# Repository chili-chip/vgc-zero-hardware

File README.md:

# chilichip console hardware (VGC Zero)

KiCad 10 project for the main board of [chilichip](https://chilichip.eu)'s open hardware keychain game console, the **VGC Zero**. A Waveshare RP2350-Plus runs the console and charges its LiPo; the display, buttons, audio and Wi-Fi/Bluetooth are modules that solder or plug onto this board. Firmware and games are built with the [chili-chip 32blit SDK](https://github.com/chili-chip/32blit-sdk) (board `chilichip_vgc`).

**Documentation: [hardware.chilichip.eu](https://hardware.chilichip.eu)** (specifications, pin map, modules, build guide). Source in [`docs/`](docs/).

Current revision: **v3.0.0**. The schematic (`vgc-zero.kicad_sch`) is the source of truth for everything below.

| Front | Back |
|:---:|:---:|
|  |  |

## Specifications

| | |
|---|---|
| Board | 50 × 100 mm, 2 layers, 1.6 mm, GND pour on both layers. About 19 mm thick assembled (display front to battery back) |
| MCU | [Waveshare RP2350-Plus](https://www.waveshare.com/wiki/RP2350-Plus) (RP2350A, USB-C, Pico-compatible pinout), soldered flat on the back by its castellated edge |
| Display | Waveshare 1.5" RGB OLED (SSD1351, 128 × 128, SPI) on the front |
| Buttons | [chili-buttons-module](https://github.com/chili-chip/chili-buttons-module-hardware): D-pad, A/B, X/Y, Start/Select, soldered flat on the front |
| Audio | [chili-audio-module](https://github.com/chili-chip/chili-audio-module-hardware): MAX98357A I²S class D amplifier, soldered flat on the back |
| Sensors | [chili-utility-module](https://github.com/chili-chip/chili-utility-module-hardware): 6-axis IMU, RTC backed by the LiPo (through VSYS), SMD haptic motor, all on I²C; soldered flat on the back beside the MCU |
| Wireless | Raspberry Pi Radio Module 2 (RM2, CYW43439): Wi-Fi 4 and Bluetooth 5.2, on the back with its antenna at the bottom edge over a copper keep-out |
| Power | 1-cell LiPo, LP802540 (8.0 × 25 × 40 mm, ~800 mAh), flat on the back between the MCU and the RM2. It plugs into the RP2350-Plus's PH1.25 battery header and charges from USB-C at 1 A, about 1.25C; replace R13 on the RP2350-Plus (160 kΩ) with about 200 kΩ to charge at about 0.8 A (1C). The RP2350-Plus's 3.3 V output supplies all modules |

## Parts

| Ref | Part | Side | Notes |
|-----|------|------|-------|
| U1 | [Waveshare RP2350-Plus](https://www.waveshare.com/wiki/RP2350-Plus) | back | `vgc-zero-footprints:RP2350-Plus`: the Pico hand-solder lands without the SWD pads, plus clearance holes for the USB-C shell legs and pegs under the module |
| U2 | [chili-audio-module](https://github.com/chili-chip/chili-audio-module-hardware) v1.1+ | back | castellated, 11.5 × 17.5 mm |
| U3 | [Raspberry Pi Radio Module 2](https://www.raspberrypi.com/products/radio-module-2/) | back | `RF_Module:RMC20452T` |
| U4 | [Waveshare 1.5inch RGB OLED Module](https://www.waveshare.com/wiki/1.5inch_RGB_OLED_Module) | front | 7-pin 2.54 mm header plus four mounting holes |
| U5 | [chili-buttons-module](https://github.com/chili-chip/chili-buttons-module-hardware) v1.2+ | front | castellated, 50 × 39 mm |
| U6 | [chili-utility-module](https://github.com/chili-chip/chili-utility-module-hardware) v2.0+ | back | castellated, 16.4 × 14.8 mm, six lands; between the MCU, R2/R3, a display mounting hole and the battery |
| BT1 | LiPo LP802540, ~800 mAh, with PCM and a PH1.25 2-pin plug | back | stuck down with double-sided tape; plugs into U1's battery header. Board-only footprint for its outline and 3D model |
| R2 | 470 Ω, axial | back | RM2 DO to the shared data line |
| R3 | 10 kΩ, axial | back | RM2 nIRQ to the shared data line |

The RM2 is wired like the Pico W radio: one GPIO (WIFI_DIO) drives DI directly and reads DO and nIRQ through R2 and R3.

## Pin map

GPIOs were chosen so every trace runs as short and straight as possible to its module. The display sits on hardware SPI1, and the Wi-Fi signals sit on SPI1's SCK/TX/CSn pins; the RM2's driver (cyw43) runs it from PIO.

| GPIO | Module pin | Signal | Notes |
|------|----------|--------|-------|
| GP0 | 1 | UTIL_SDA | I2C0 SDA; pull-up on the module |
| GP1 | 2 | UTIL_SCL | I2C0 SCL; pull-up on the module |
| GP2 | 4 | UTIL_INT | open-drain IMU/RTC interrupt; pull-up on the module |
| GP3 | 5 | AUDIO_DIN | I²S data |
| GP4 | 6 | AUDIO_BCLK | I²S bit clock |
| GP5 | 7 | AUDIO_LRCLK | I²S word select (BCLK + 1, as the PIO I²S driver expects) |
| GP6 | 9 | AUDIO_MODE | amplifier enable (high = on, mono mix) |
| GP7 | 10 | BTN_A | |
| GP8 | 11 | BTN_B | |
| GP9 | 12 | WIFI_ON | RM2 WL_ON and BT_ON |
| GP10 | 14 | BTN_Y | |
| GP11 | 15 | BTN_X | |
| GP12 | 16 | BTN_SELECT | |
| GP13 | 17 | WIFI_CS | SPI1 CSn |
| GP14 | 19 | WIFI_CLK | SPI1 SCK |
| GP15 | 20 | WIFI_DIO | SPI1 TX; DI direct, DO via R2, nIRQ via R3 |
| GP16 | 21 | BTN_DOWN | |
| GP17 | 22 | BTN_RIGHT | |
| GP18 | 24 | BTN_START | |
| GP19 | 25 | BTN_UP | |
| GP20 | 26 | BTN_LEFT | |
| GP21 | 27 | DISP_RST | |
| GP22 | 29 | DISP_DC | |
| GP26 | 31 | DISP_CLK | SPI1 SCK |
| GP27 | 32 | DISP_DIN | SPI1 TX |
| GP28 | 34 | DISP_CS | |

The utility module's RTC backup (VBAT, land 6) is wired to VSYS (RP2350-Plus pin 39), which stays powered from the LiPo while the console is off. The utility module takes GP0/GP1, the default UART0 pins, so use USB serial for debug output. Its I²C addresses are 0x6A (IMU), 0x52 (RTC) and 0x5A (haptic driver). Buttons short to GND when pressed and have no pull-ups on the module, so enable the RP2350's internal pull-ups.

## Ordering the PCB from JLCPCB

Every tagged release has `chilichip-console-<version>-gerbers.zip` (Gerbers and drill) and `chilichip-console-<version>-bom.csv` (hand-assembly BOM) attached.

1. Download the gerber zip from the [latest release](https://github.com/chili-chip/vgc-zero-hardware/releases/latest).
2. On [jlcpcb.com](https://jlcpcb.com/), click **Order now** and upload the zip.
3. Choose 2 layers and 1.6 mm thickness. HASL is fine; ENIG is nicer for soldering the castellated modules flat. Everything else can stay at the defaults.
4. Leave **PCB Assembly** off: every part on this board is soldered by hand.

The audio, buttons and utility modules are separate boards. Order them from their own repositories.

To build the files from a local checkout instead, run `scripts/export-jlcpcb.sh` (needs KiCad 10's `kicad-cli` and `zip`). They're written to `production/`.

## Assembly

1. **Back side:** solder the RP2350-Plus flat by its castellations, then the RM2, the audio module, the utility module and R2/R3. Stick the LiPo down in its outline and plug it into the RP2350-Plus's battery header.
2. **Front side:** solder the buttons module flat by its castellations, then fit the display on its 7-pin header and fix it with the four mounting holes.
3. Keep the area past the RM2's antenna clear: no metal, cables or fingers over the keep-out at the bottom edge.

## Repository layout

| Path | Contents |
|------|----------|
| `vgc-zero.kicad_*` | KiCad 10 schematic, PCB and project |
| `vgc-zero-symbols.kicad_sym`, `vgc-zero-footprints.pretty/` | Project symbols and footprints (module outlines and castellation lands) |
| `RPI_RMC20452T.kicad_sym` | Official RM2 symbol from Raspberry Pi |
| `3d-models/` | STEP models of the modules (display, audio, buttons, utility, RM2), the RP2350-Plus (Waveshare's model, gzipped as `.stpZ`) and the LiPo envelope |
| `vgc-zero.glb` | 3D export of the assembled board |
| `scripts/export-jlcpcb.sh` | Builds the gerber zip and BOM |
| `scripts/render-images.sh` | Regenerates the renders, placement drawings and schematic in `docs/`, and `vgc-zero.glb` |
| `docs/`, `mkdocs.yml` | Documentation site ([hardware.chilichip.eu](https://hardware.chilichip.eu)) |
| `docs/next-revision.md` | The plan this revision implemented |
| `.github/workflows/main.yml` | CI and release workflow |
| `.github/workflows/docs.yml` | Builds the docs site and deploys it to Cloudflare Pages |

CI runs ERC, DRC and the JLCPCB export on every push and pull request. Pushing a `v*` tag publishes a GitHub release with the schematic PDF, a PCB image, Gerbers and the JLCPCB files.

## Earlier revisions

Board v2.0.0 (50 × 90 mm) used a Raspberry Pi Pico 2 and USB power only, with no battery and no utility module.

Board v1.1.4 used a Waveshare RP2350-Plus, ten through-hole tactile buttons, a buzzer, an LED and a JST cable to the display. The first prototype was built on a breadboard: see the [breadboard guide](https://chilichip.eu/docs/vgc-zero/vgc-breadboard/).

## License

MIT, see [LICENSE](LICENSE).

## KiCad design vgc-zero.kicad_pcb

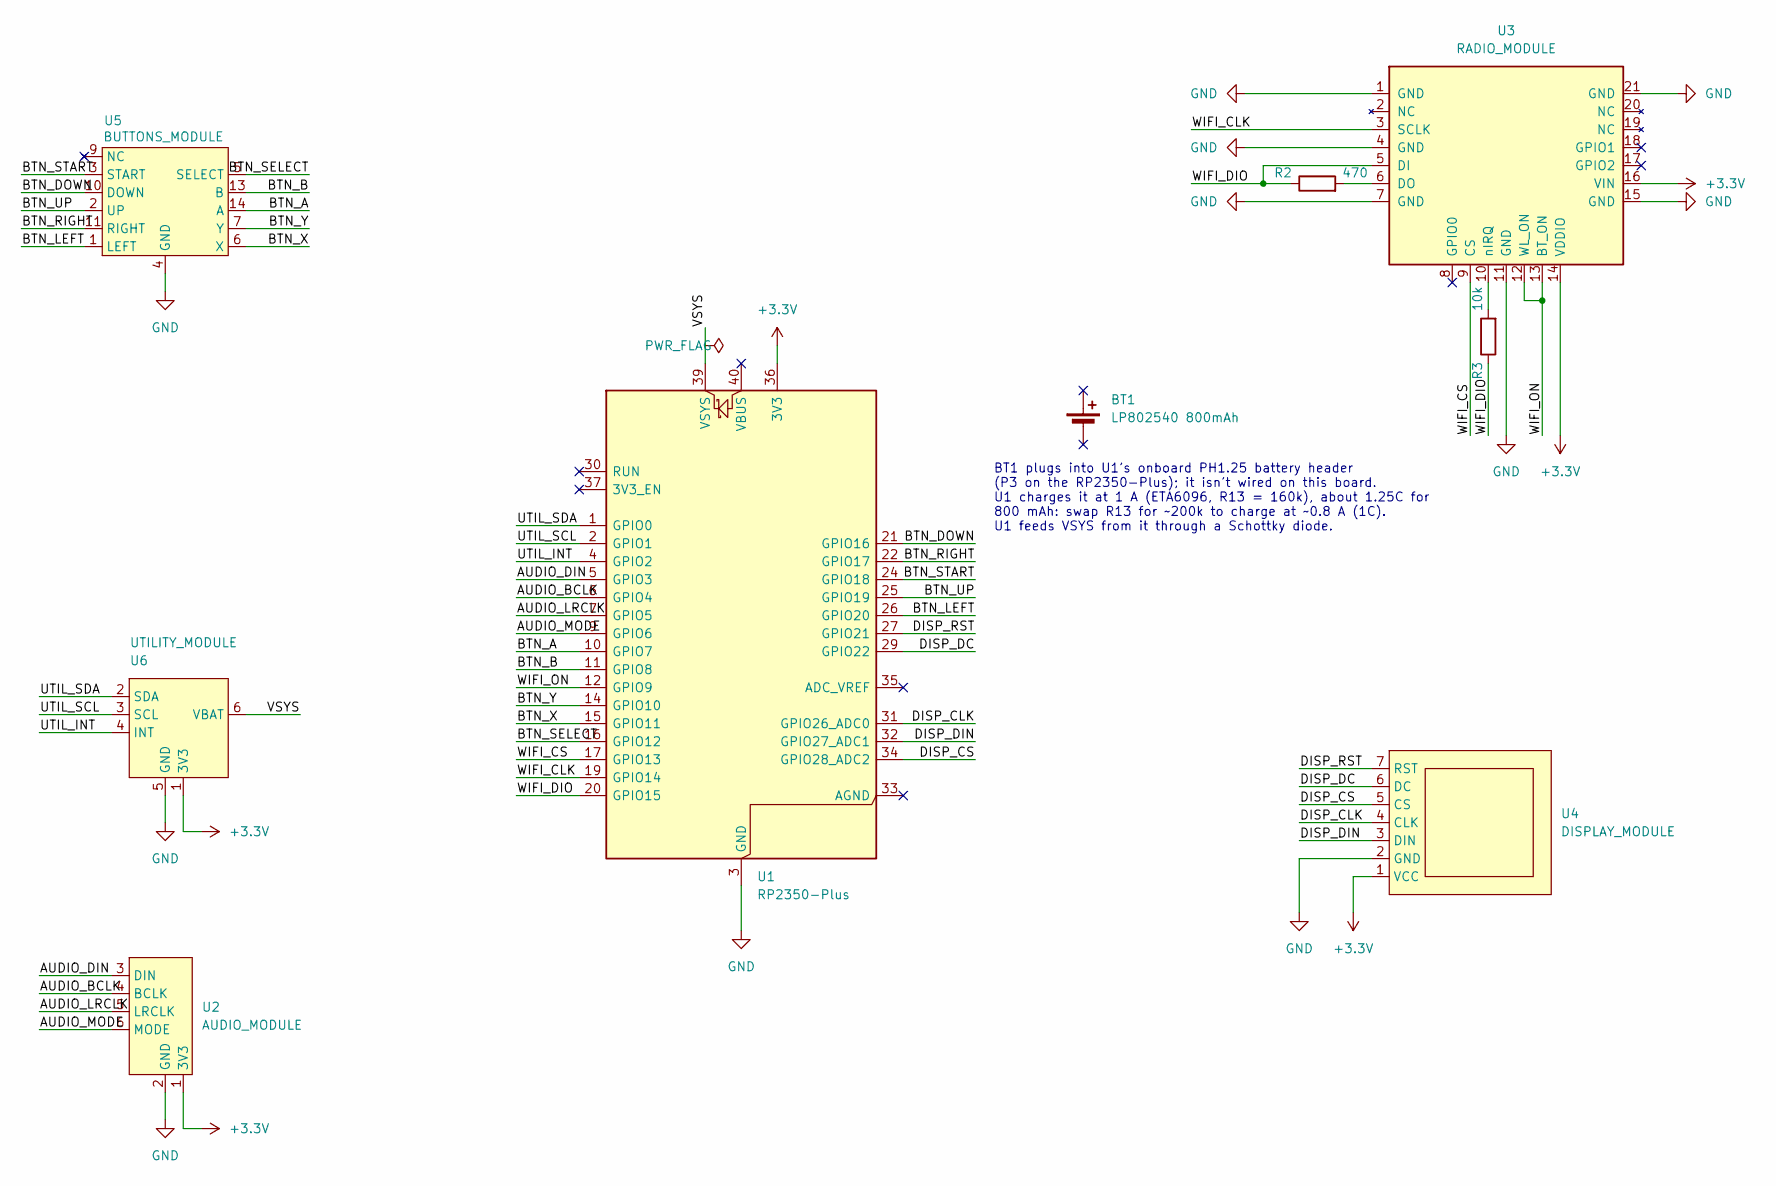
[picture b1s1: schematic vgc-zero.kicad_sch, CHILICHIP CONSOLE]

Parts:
BT1: LP802540 800mAh; LiPo_LP802540
R2: 470; R_Axial_DIN0207_L6.3mm_D2.5mm_P10.16mm_Horizontal
R3: 10k; R_Axial_DIN0207_L6.3mm_D2.5mm_P10.16mm_Horizontal
U1: RP2350-Plus
U2: AUDIO_MODULE; AudioModule
U3: RADIO_MODULE; RMC20452T
U4: DISPLAY_MODULE; SSD1351_OLED_128x128_WAVESHARE
U5: BUTTONS_MODULE; ButtonsModule
U6: UTILITY_MODULE; UtilityModule

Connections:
+3.3V: U1.36 (3V3), U2.1 (3V3), U3.14 (VDDIO), U3.16 (VIN), U4.1 (VCC), U6.1 (3V3)
/AUDIO_BCLK: U1.6 (GPIO4), U2.4 (BCLK)
/AUDIO_DIN: U1.5 (GPIO3), U2.3 (DIN)
/AUDIO_LRCLK: U1.7 (GPIO5), U2.5 (LRCLK)
/AUDIO_MODE: U1.9 (GPIO6), U2.6 (MODE)
/BTN_A: U1.10 (GPIO7), U5.14 (A)
/BTN_B: U1.11 (GPIO8), U5.13 (B)
/BTN_DOWN: U1.21 (GPIO16), U5.10 (DOWN)
/BTN_LEFT: U1.26 (GPIO20), U5.1 (LEFT)
/BTN_RIGHT: U1.22 (GPIO17), U5.11 (RIGHT)
/BTN_SELECT: U1.16 (GPIO12), U5.5 (SELECT)
/BTN_START: U1.24 (GPIO18), U5.3 (START)
/BTN_UP: U1.25 (GPIO19), U5.2 (UP)
/BTN_X: U1.15 (GPIO11), U5.6 (X)
/BTN_Y: U1.14 (GPIO10), U5.7 (Y)
/DISP_CLK: U1.31 (GPIO26_ADC0), U4.4 (CLK)
/DISP_CS: U1.34 (GPIO28_ADC2), U4.5 (CS)
/DISP_DC: U1.29 (GPIO22), U4.6 (DC)
/DISP_DIN: U1.32 (GPIO27_ADC1), U4.3 (DIN)
/DISP_RST: U1.27 (GPIO21), U4.7 (RST)
/UTIL_INT: U1.4 (GPIO2), U6.4 (INT)
/UTIL_SCL: U1.2 (GPIO1), U6.3 (SCL)
/UTIL_SDA: U1.1 (GPIO0), U6.2 (SDA)
/VSYS: U1.39 (VSYS), U6.6 (VBAT)
/WIFI_CLK: U1.19 (GPIO14), U3.3 (SCLK)
/WIFI_CS: U1.17 (GPIO13), U3.9 (CS)
/WIFI_DIO: R2.1, R3.1, U1.20 (GPIO15), U3.5 (DI)
/WIFI_ON: U1.12 (GPIO9), U3.12 (WL_ON), U3.13 (BT_ON)
GND: U1.3 (GND), U1.8 (GND), U1.13 (GND), U1.18 (GND), U1.23 (GND), U1.28 (GND), U1.38 (GND), U2.2 (GND), U3.1 (GND), U3.4 (GND), U3.7 (GND), U3.11 (GND), U3.15 (GND), U3.21 (GND), U4.2 (GND), U5.4 (GND), U5.8 (GND), U5.12 (GND), U5.15 (GND), U5.16 (GND), U6.5 (GND)
unnamed: R2.2, U3.6 (DO)
unnamed: R3.2, U3.10 (nIRQ)

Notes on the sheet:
BT1 plugs into U1's onboard PH1.25 battery header (P3 on the RP2350-Plus); it isn't wired on this board. U1 charges it at 1 A (ETA6096, R13 = 160k), about 1.25C for 800 mAh: swap R13 for ~200k to charge at ~0.8 A (1C). U1 feeds VSYS from it through a Schottky diode.

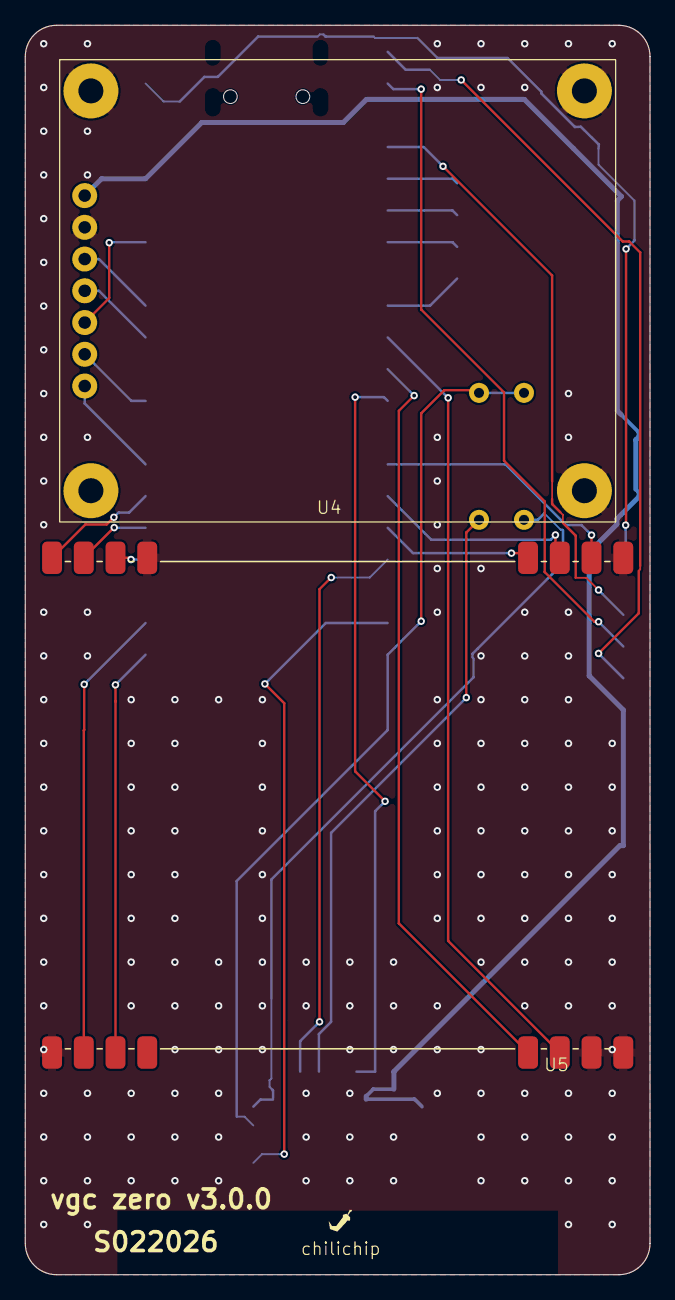
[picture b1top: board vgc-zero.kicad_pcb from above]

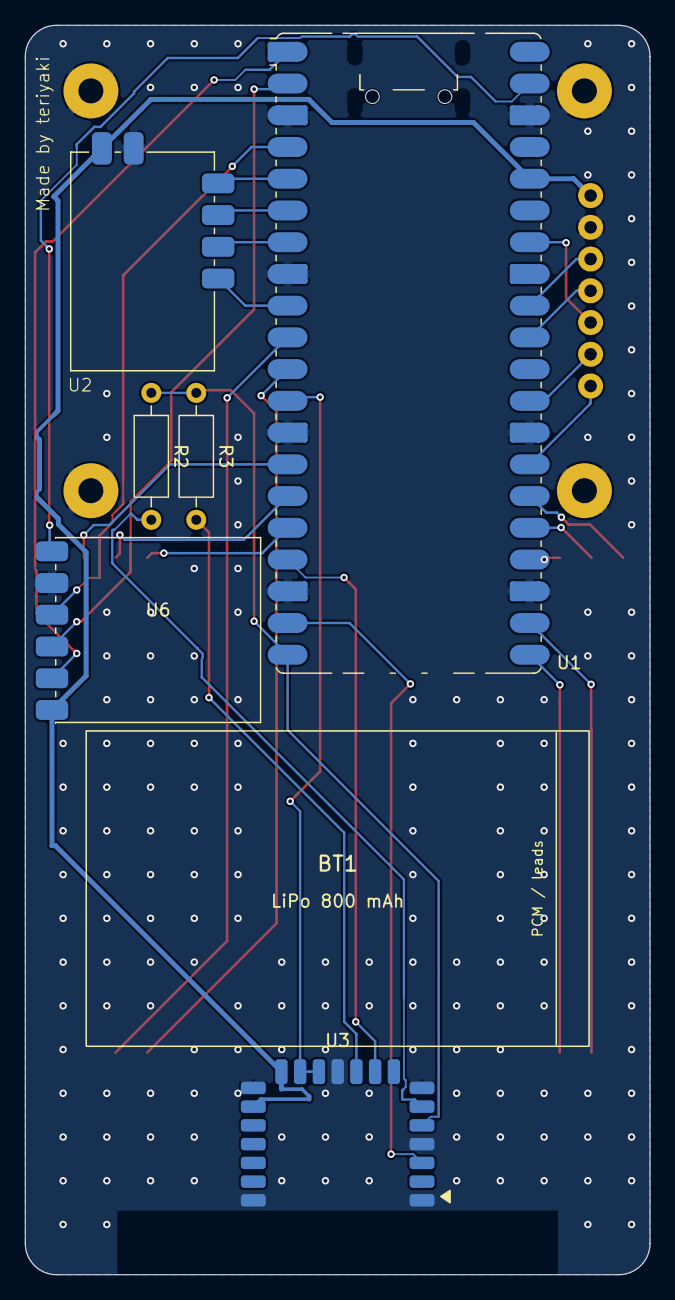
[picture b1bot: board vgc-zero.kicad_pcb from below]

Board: 2 copper layers, 50.0 x 100.0 mm, 9 parts (7 on the bottom side), 31 nets.

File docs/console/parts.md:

# Parts list

Everything you need for one console built on main board v3.0.0. Each release of this repository also has a hand-assembly BOM attached as `chilichip-console-<version>-bom.csv`.

Prices change too often to list here. The links point to where the team bought the parts.

## Main board

| Ref | Qty | Part | Notes | Where to get it |
|---|---|---|---|---|
| PCB | 1 | Main board v3.0.0 | 2 layers, 1.6 mm, 50 × 100 mm | [JLCPCB](https://jlcpcb.com/), gerbers on the [release](https://github.com/chili-chip/vgc-zero-hardware/releases/tag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 |
| U1 | 1 | Waveshare RP2350-Plus, **16 MB** | Soldered flat by its castellations. The console firmware expects 16 MB of flash | [Waveshare](https://www.waveshare.com/wiki/RP2350-Plus) |
| U4 | 1 | Waveshare 1.5inch RGB OLED Module | SSD1351, 128 × 128, with its 7-pin header | [Waveshare](https://www.waveshare.com/wiki/1.5inch_RGB_OLED_Module) |
| U3 | 1 | Raspberry Pi Radio Module 2 | Castellated, soldered flat | [Raspberry Pi resellers](https://www.raspberrypi.com/products/radio-module-2/), for example The Pi Hut |
| U2 | 1 | chili-audio-module v1.1.1 | Assembled by JLCPCB | [Audio module](../modules/audio.md#ordering) |
| U5 | 1 | chili-buttons-module v1.2.0 | Bare ENIG PCB, no parts | [Buttons module](../modules/buttons.md#ordering) |
| U6 | 1 | chili-utility-module v2.0.0 | Assembled by JLCPCB | [Utility module](../modules/utility.md#ordering) |
| R2 | 1 | 470 Ω resistor, axial, 0.25 W | RM2 DO to the shared data line | Any electronics shop |
| R3 | 1 | 10 kΩ resistor, axial, 0.25 W | RM2 nIRQ to the shared data line | Any electronics shop |
| BT1 | 1 | LiPo LP802540, ~800 mAh, with protection and PH1.25 plug | 8.0 × 25 × 40 mm | Sold as "802540" cells, for example by Heltec resellers |

## Extras

| Qty | Part | Notes |
|---|---|---|
| 1 | Speaker, 4 to 8 Ω, with a Molex PicoBlade 1.25 mm 2-pin plug | Plugs into J3 on the audio module |
| 1 set | Game Boy Advance silicone button pads | D-pad, A/B and Start/Select pads. See [buttons](../modules/buttons.md#rubber-pads) |
| 1 set | GBA button caps and D-pad | For the shell |
| 4 | Screws and standoffs for the display | Fit the 2 mm holes |
| 1 | Double-sided foam tape | Holds the battery |
| 1 | USB-C cable | Power, charging and data |

## What JLCPCB assembles

| Board | PCB options | Assembly | Parts on it |
|---|---|---|---|
| Main board | 2 layers, 1.6 mm, HASL or ENIG | None | None: hand-soldered |
| Audio module | 2 layers, 1.6 mm, castellated holes, ENIG recommended | Top side | 5 parts, all LCSC |
| Utility module | 2 layers, 1.6 mm, castellated holes | Top side | 15 parts; the motor M1 is not on LCSC (global sourcing or consigned) |
| Buttons module | 2 layers, 1.6 mm, castellated holes, **ENIG required** | None | None |

## Module BOMs

Each module page has its full bill of materials with LCSC part numbers:

- [Audio module BOM](../modules/audio.md#bill-of-materials)
- [Utility module BOM](../modules/utility.md#bill-of-materials)
- [Buttons module](../modules/buttons.md) has no parts.

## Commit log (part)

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2025-12-10 Create pcb design
2025-12-10 move symbols to project library
2025-12-10 fix pro
2025-12-10 pcb done
2025-12-11 move via off the pad
2025-12-11 Add GitHub Actions workflow for KiCad 9 CI
2025-12-11 Refactor output paths in GitHub Actions workflow
    Updated output directory paths for schematic and gerbers.
2025-12-11 Add release job for uploading KiCad artifacts
    Added a new job to upload KiCad artifacts to GitHub releases when a release is published.
2025-12-11 Remove condition to skip CI on release events
2025-12-11 Modify GitHub Actions for CI and release process
    Updated CI workflow to include release tagging and artifact uploads.
2025-12-11 Add permissions for release job in workflow
2025-12-11 Package Gerbers as zip and tar.gz
    Added steps to package Gerbers into zip and tar.gz formats before creating a GitHub release.
2025-12-11 Add MIT License to the project
2025-12-11 add markings
2025-12-11 final touches
2025-12-11 bump all the way to 1.0.0
2025-12-11 minor fixes
2026-03-03 adjust display pins
2026-03-03 bump version
2026-03-05 major improvements
2026-03-06 minor improvements
2026-03-06 fix overlap
